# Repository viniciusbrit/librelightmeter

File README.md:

# librelightmeter
A light meter designed for analog photography based on a BH1751 ambient light sensor running off of an ATMega328P microcontroller.

### Current Iteration: Prototype 0.2 [TESTING ONGOING]

The 3D models in the repository are of this prototype, which was made with several off the shelf parts in a protoboard. They are there for archival purposes only.

### Project Goals
* Build a compact, accurate handheld light meter.
* Design several alternatives, for hotshoe mounting and incident measuring.

### Project Progress
- [x] Build A Prototype.
- [x] Find Sensor With Enough Range.
  > Decided on the BH1751 for it's better measurement range.
- [x] Find Adequate Cheap Microcontroller.
  > Decided on the ATMega328P-AU due to it's popularity.
- [ ] Build Prototype With New Parts.
- [ ] Design Version 1.0 Handheld PCB.
- [ ] Write Full Firmware.
- [ ] Design Hot-Shoe Mounted Alternative.
- [ ] Add Incident Metering To Handheld Model.

### Licenses
* CERN Open Hardware Licence Version 2.0 - Strongly Reciprocal.
* GNU GENERAL PUBLIC LICENSE Verson 3.0.

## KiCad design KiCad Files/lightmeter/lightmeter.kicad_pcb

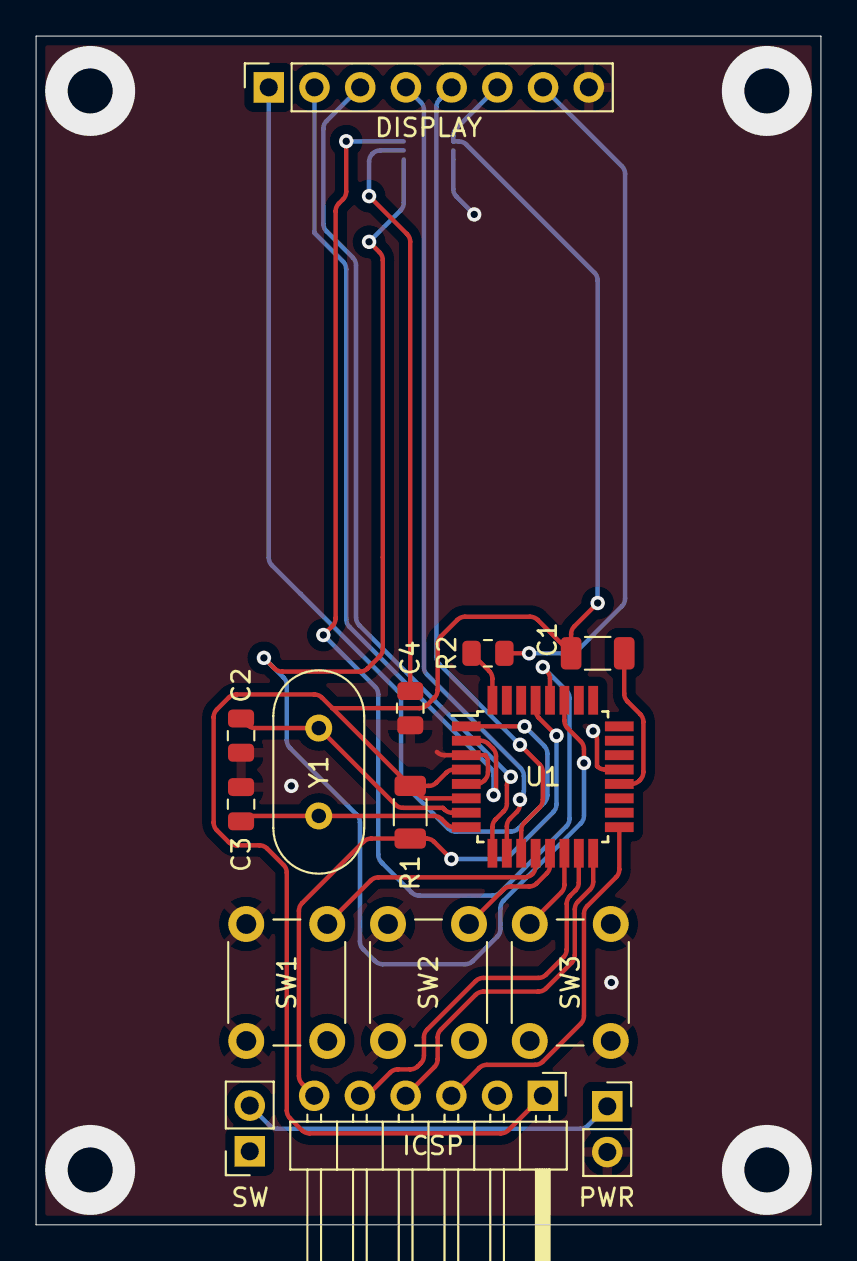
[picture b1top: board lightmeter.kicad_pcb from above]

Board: 2 copper layers, 43.6 x 66.0 mm, 16 parts (1 on the bottom side), 23 nets.

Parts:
C1: 47uF; C_1206_3216Metric
C2, C3: 22pF; C_0805_2012Metric
C4: 0.1uF; C_0805_2012Metric
DISPLAY: Conn_01x08; PinSocket_1x08_P2.54mm_Vertical
ICSP: Conn_01x06; PinHeader_1x06_P2.54mm_Horizontal
PWR: Conn_01x02_Female; PinSocket_1x02_P2.54mm_Vertical
R1: 1k; R_1206_3216Metric
R2: 220; R_0805_2012Metric
SW: SW_Push_SPDT; PinSocket_1x02_P2.54mm_Vertical
SW1, SW2, SW3: SW_Push; SW_PUSH_6mm
U1: ATmega328P-A; TQFP-32_7x7mm_P0.8mm
U2: BH1750FVI-TR; XDCR_BH1750FVI-TR
Y1: 16Mhz; Crystal_HC49-U_Vertical

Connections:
BAT+: PWR.1, SW.2 (B)
BL: R2.1, U1.32 (PD2)
CE: DISPLAY.2, U1.2 (PD4)
CLK: DISPLAY.5, U1.11 (PD7)
CS: ICSP.6, R1.1, U1.29 (~RESET/PC6)
DC: DISPLAY.3, U1.9 (PD5)
DIN: DISPLAY.4, U1.10 (PD6)
GND: C2.2, C3.2, C4.1, DISPLAY.8, ICSP.2, PWR.2, SW1.2, SW2.2, SW3.2, U1.3 (GND), U1.5 (GND), U1.21 (GND), U2.2 (ADDR), U2.3 (GND)
MISO: ICSP.4, U1.16 (PB4)
MOSI: ICSP.5, U1.15 (PB3)
unnamed: DISPLAY.7, R2.2
unnamed: SW1.1, U1.12 (PB0)
unnamed: SW2.1, U1.13 (PB1)
unnamed: SW3.1, U1.14 (PB2)
unnamed: C2.1, U1.7 (XTAL1/PB6), Y1.1
unnamed: C3.1, U1.8 (XTAL2/PB7), Y1.2
unnamed: C1.1, U1.20 (AREF)
unnamed: C4.2, U2.5 (DVI)
RST: DISPLAY.1, U1.1 (PD3)
SCK: ICSP.3, U1.17 (PB5)
SCL: U1.28 (PC5), U2.6 (SCL)
SDA: U1.27 (PC4), U2.4 (SDA)
VCC: C1.2, DISPLAY.6, ICSP.1, R1.2, U1.4 (VCC), U1.6 (VCC), U2.1 (VCC)

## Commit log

2022-05-27 Add shell 3D models.
2022-05-27 Add Arduino spaghetti code
2022-06-29 General Project Update
    Changed project name.
    Changed project progress goals.
    Included licenses.
2022-06-29 Create HARDWARE_LICENSE
2022-06-29 Changed issues into checklist
2022-06-30 Add KiCad Project Files
    Includes Revision 0.2 Prototype PCB.
